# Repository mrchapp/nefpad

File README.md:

# NefPad

## Components
* 1 Arduino Pro Micro
* 1 IC socket (optional)
* 19 diodes
* 2 100 nF ceramic capacitors
* 1 momentary switch
* 8 SK6812 mini
* 17 hotswap sockets
* 17 MX switches
* 15 1U keycaps
* 2 2U keycaps
* 1 rotary encoder EC11
* 1 knob

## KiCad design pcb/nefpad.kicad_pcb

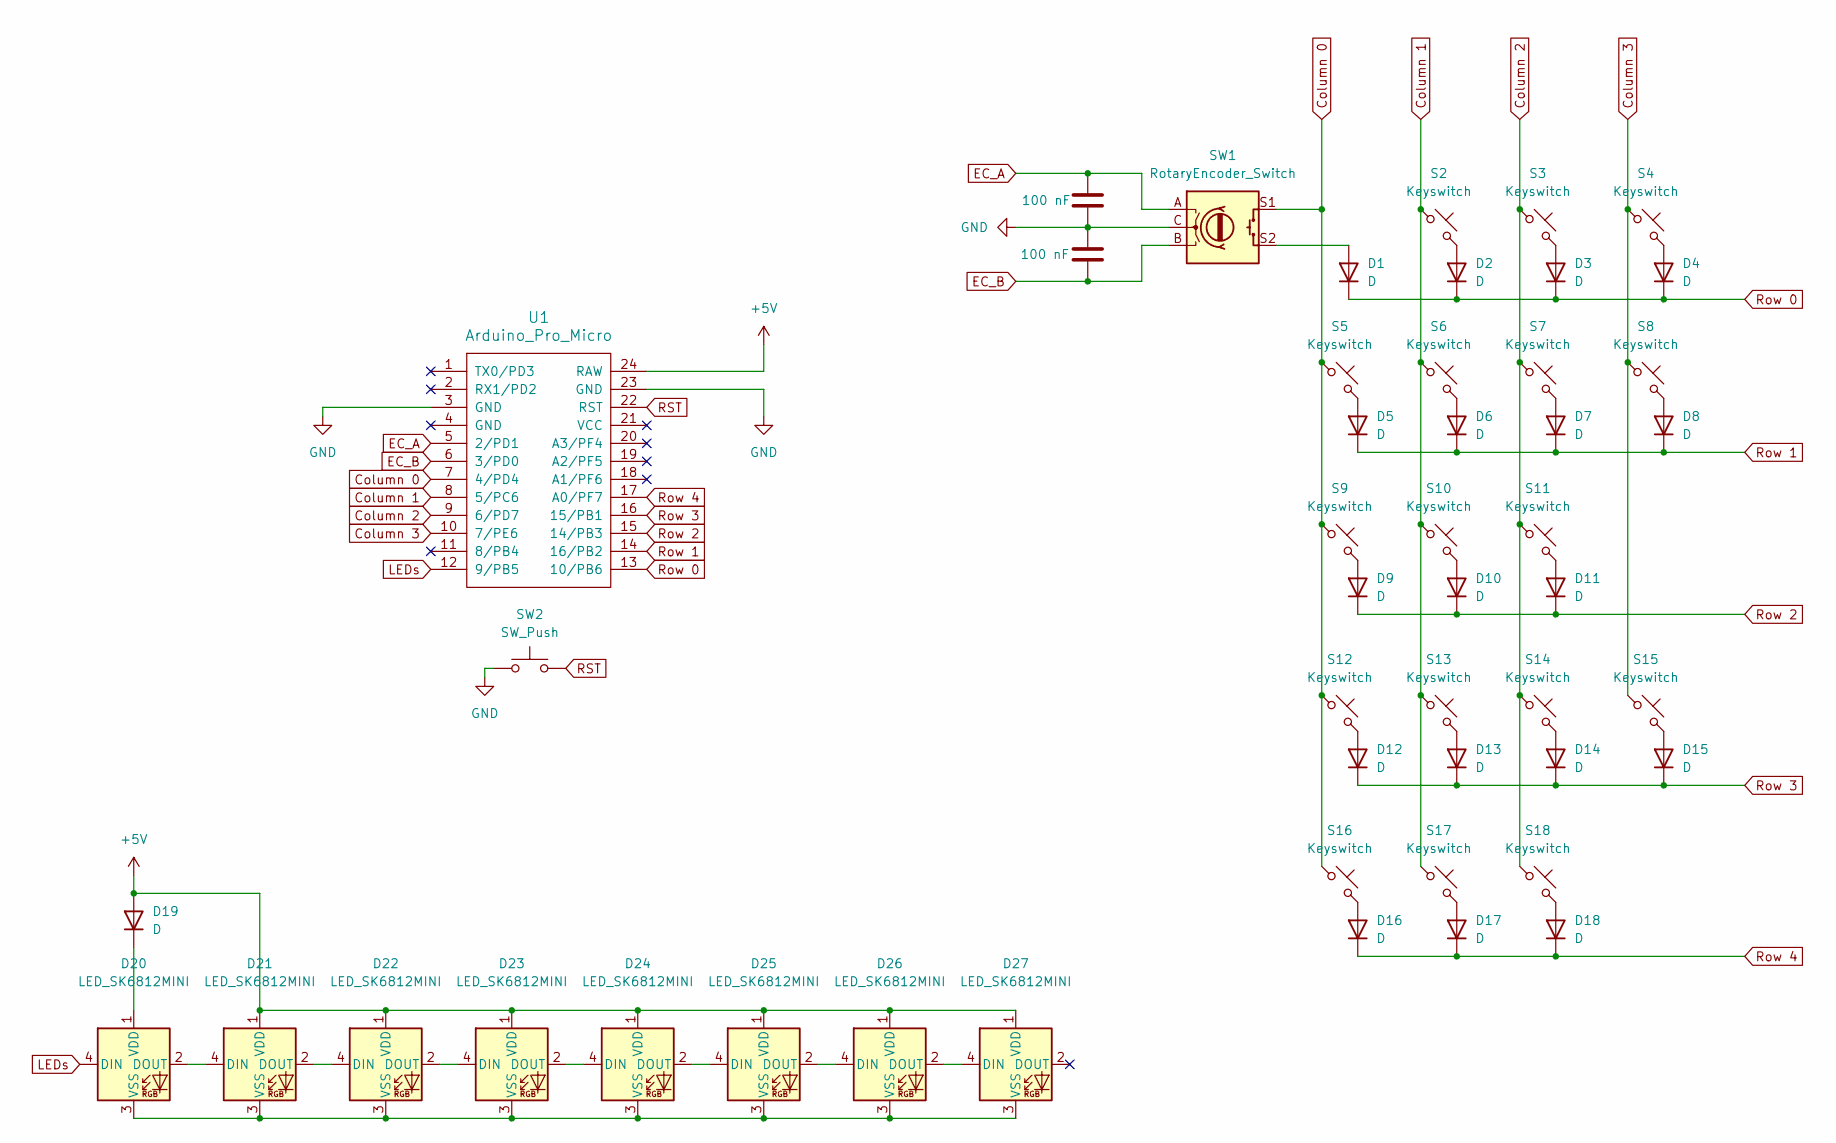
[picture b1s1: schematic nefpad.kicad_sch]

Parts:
C1, C2: 100 nF; C_Disc_D4.3mm_W1.9mm_P5.00mm
D1, D2, D3, D4, D5, D6, D7, D8, D9, D10, D11, D12, D13, D14, D15, D16, D17, D18, D19: D; D_DO-35_SOD27_P7.62mm_Horizontal
D20, D21, D22, D23, D24, D25, D26, D27: LED_SK6812MINI
S2, S3, S4, S5, S6, S7, S9, S10, S11, S12, S13, S14, S16, S17, S18: Keyswitch; Hotswap_MX_1.00u
S8, S15: Keyswitch; Hotswap_MX_2.00u_90deg
SW1: RotaryEncoder_Switch; RotaryEncoder_Alps_EC11E-Switch_Vertical_H20mm
SW2: SW_Push; SW_PUSH_6mm
U1: Arduino_Pro_Micro

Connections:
+5V: D19.2 (A), D21.1 (VDD), D22.1 (VDD), D23.1 (VDD), D24.1 (VDD), D25.1 (VDD), D26.1 (VDD), D27.1 (VDD), U1.24 (RAW)
Column 0: S5.1, S9.1, S12.1, S16.1, SW1.S1, U1.7 (4/PD4)
Column 1: S2.1, S6.1, S10.1, S13.1, S17.1, U1.8 (5/PC6)
Column 2: S3.1, S7.1, S11.1, S14.1, S18.1, U1.9 (6/PD7)
Column 3: S4.1, S8.1, S15.1, U1.10 (7/PE6)
EC_A: C1.1, SW1.A, U1.5 (2/PD1)
EC_B: C2.2, SW1.B, U1.6 (3/PD0)
GND: C1.2, C2.1, SW1.C, SW2.1, U1.3 (GND), U1.23 (GND)
LEDs: D20.4 (DIN), U1.12 (9/PB5)
unnamed: D1.2 (A), SW1.S2
unnamed: D2.2 (A), S2.2
unnamed: D3.2 (A), S3.2
unnamed: D4.2 (A), S4.2
unnamed: D5.2 (A), S5.2
unnamed: D6.2 (A), S6.2
unnamed: D7.2 (A), S7.2
unnamed: D8.2 (A), S8.2
unnamed: D9.2 (A), S9.2
unnamed: D10.2 (A), S10.2
unnamed: D11.2 (A), S11.2
unnamed: D12.2 (A), S12.2
unnamed: D13.2 (A), S13.2
unnamed: D14.2 (A), S14.2
unnamed: D15.2 (A), S15.2
unnamed: D16.2 (A), S16.2
unnamed: D17.2 (A), S17.2
unnamed: D18.2 (A), S18.2
unnamed: D19.1 (K), D20.1 (VDD)
unnamed: D20.2 (DOUT), D21.4 (DIN)
unnamed: D20.3 (VSS), D21.3 (VSS), D22.3 (VSS), D23.3 (VSS), D24.3 (VSS), D25.3 (VSS), D26.3 (VSS), D27.3 (VSS)
unnamed: D21.2 (DOUT), D22.4 (DIN)
unnamed: D22.2 (DOUT), D23.4 (DIN)
unnamed: D23.2 (DOUT), D24.4 (DIN)
unnamed: D24.2 (DOUT), D25.4 (DIN)
unnamed: D25.2 (DOUT), D26.4 (DIN)
unnamed: D26.2 (DOUT), D27.4 (DIN)
RST: SW2.2, U1.22 (RST)
Row 0: D1.1 (K), D2.1 (K), D3.1 (K), D4.1 (K), U1.13 (10/PB6)
Row 1: D5.1 (K), D6.1 (K), D7.1 (K), D8.1 (K), U1.14 (16/PB2)
Row 2: D9.1 (K), D10.1 (K), D11.1 (K), U1.15 (14/PB3)
Row 3: D12.1 (K), D13.1 (K), D14.1 (K), D15.1 (K), U1.16 (15/PB1)
Row 4: D16.1 (K), D17.1 (K), D18.1 (K), U1.17 (A0/PF7)

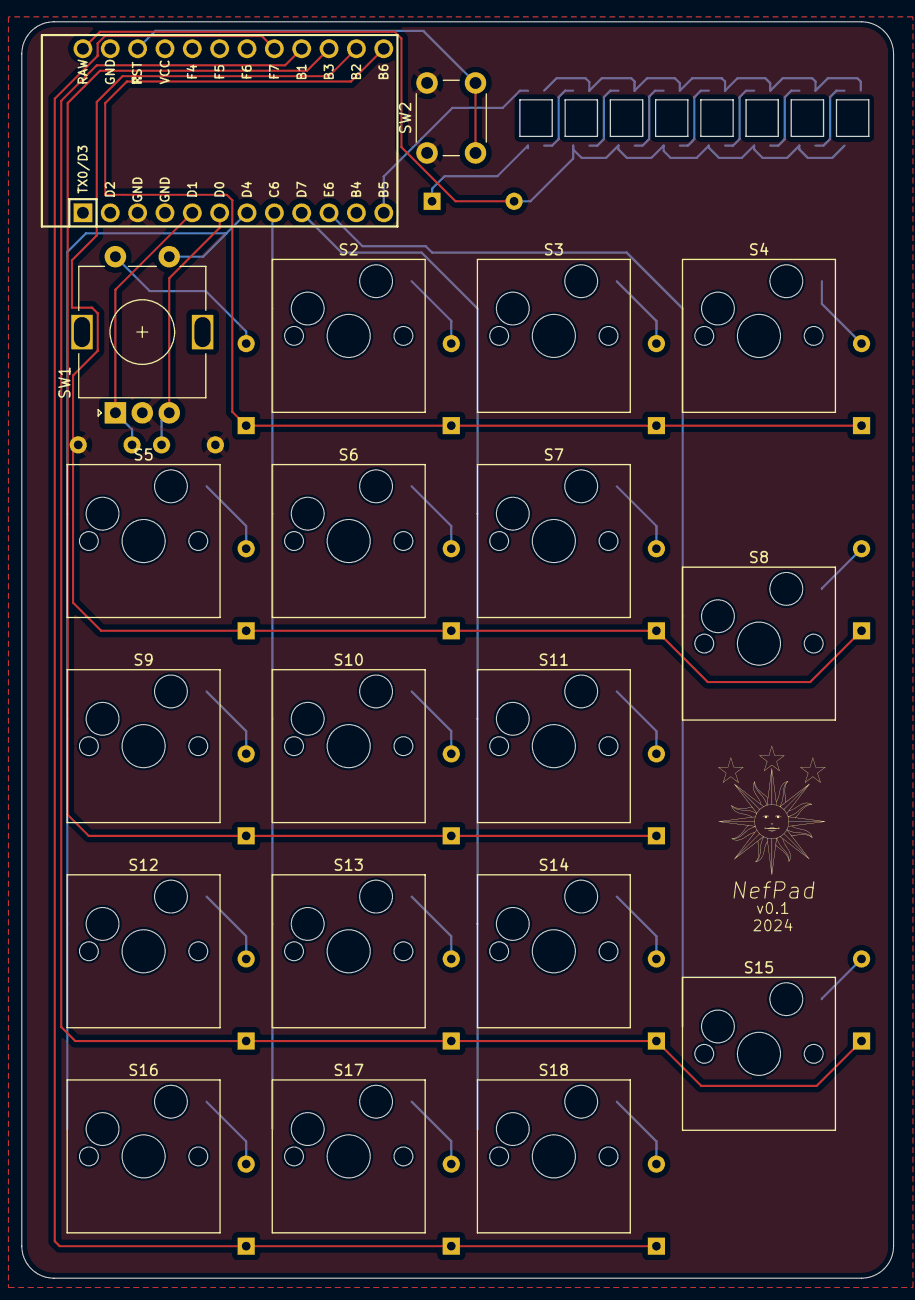
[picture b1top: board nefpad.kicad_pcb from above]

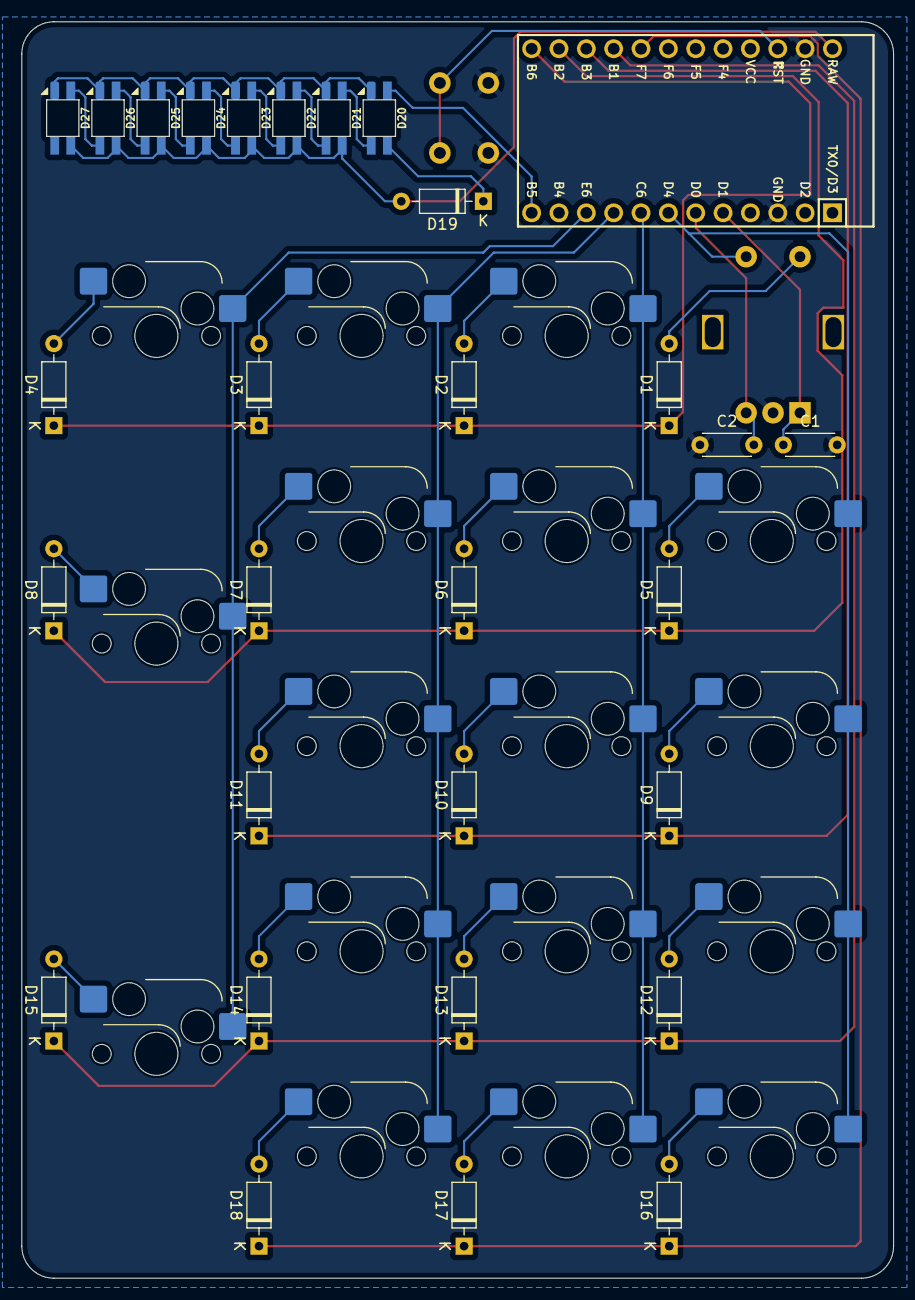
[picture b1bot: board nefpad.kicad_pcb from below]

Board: 2 copper layers, 80.9 x 116.6 mm, 49 parts (21 on the bottom side), 42 nets.

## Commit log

2024-08-08 Initial import: Version 0.1
